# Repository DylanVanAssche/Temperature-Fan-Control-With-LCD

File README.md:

Temperature Fan Control With LCD
================================

A fan controlled by a temperaturesensor and an Arduino. The current temperature (in °C) and fanpower (in %) is shown on a LCD display.

Produced by Dylan Van Assche (2013). I'm not responsible for any damage to your stuff!

Libraries for EAGLE: 
* http://www.faludi.com/2008/10/07/arduino-avr-library-for-eagle-layout-editor/
* https://github.com/zumbik/Eagle-Libraries/blob/master/lm35.lbr

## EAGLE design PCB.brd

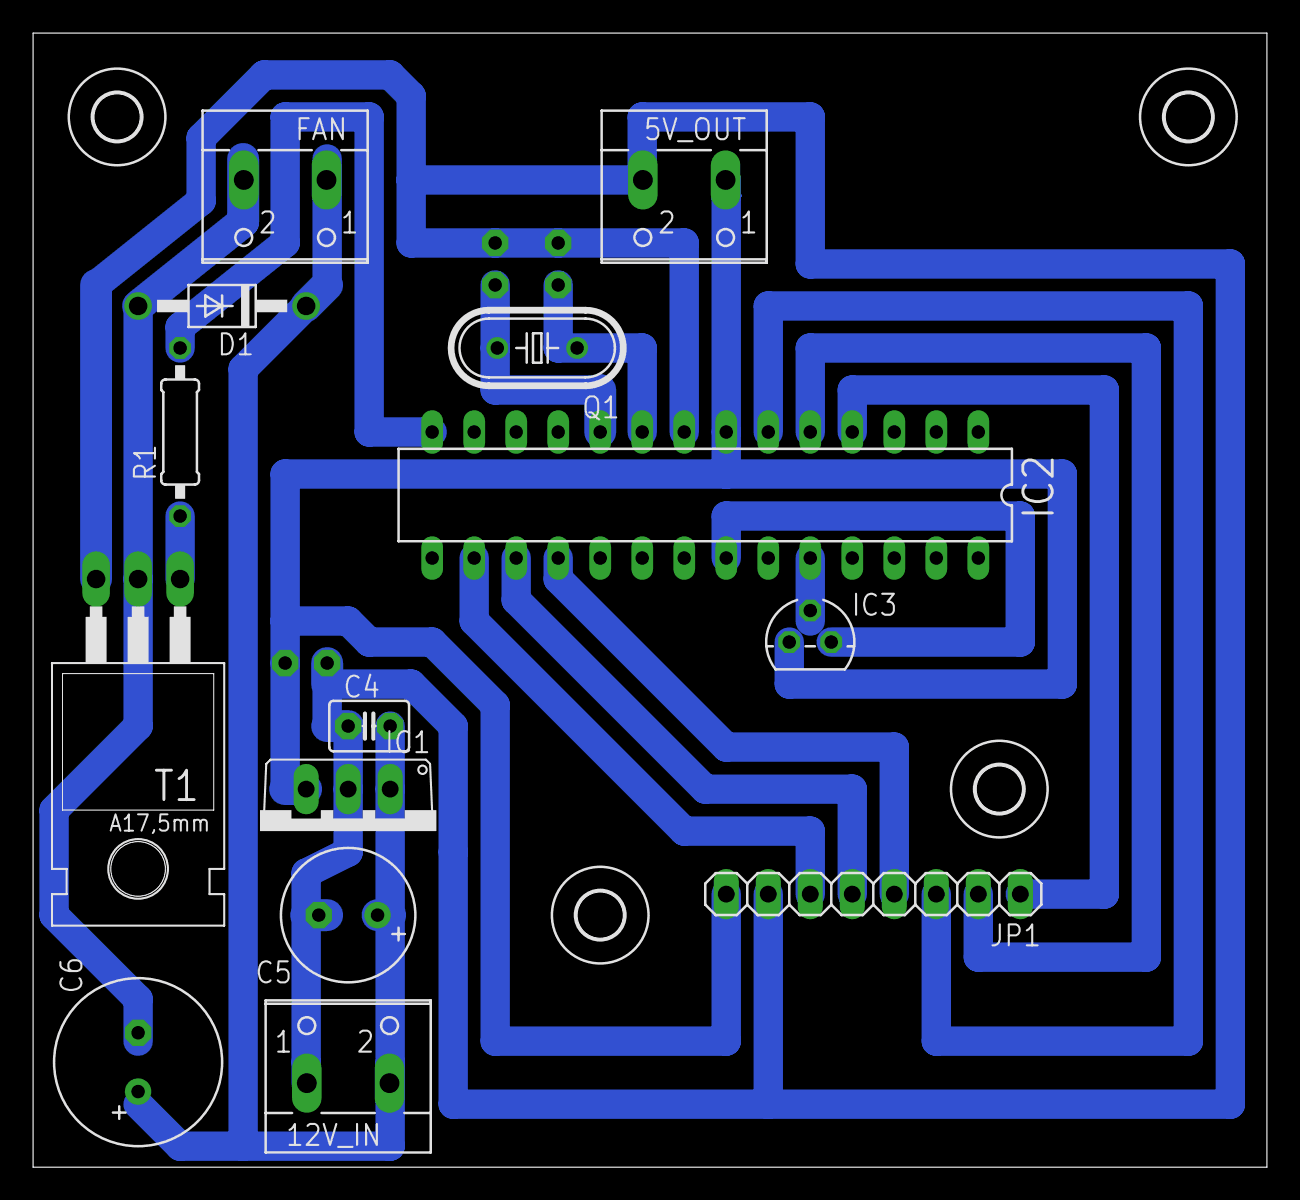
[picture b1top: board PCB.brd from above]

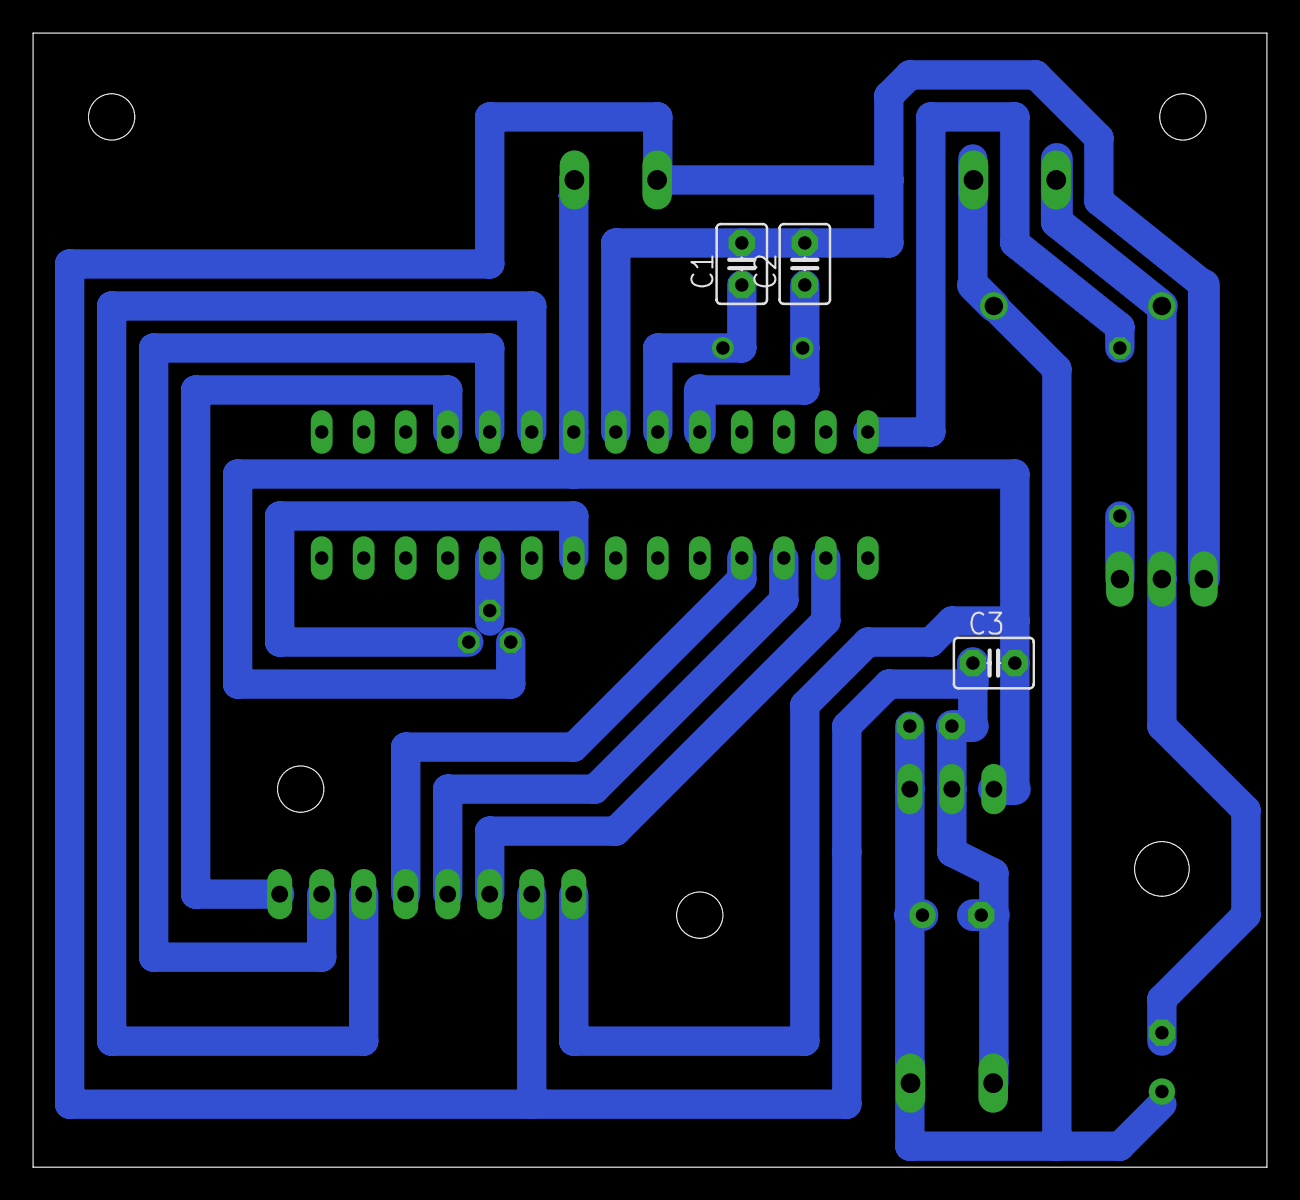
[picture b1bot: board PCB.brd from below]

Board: 2 copper layers, 74.6 x 68.6 mm, 21 parts (3 on the bottom side), 16 nets.

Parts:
5V_OUT, 12V_IN: W237-102
C1, C2: 22 pF; C2.5-3
C3, C4: 100 nF; C2.5-3
C5: 1000 uF; E3,5-8
C6: 2200uF; E3,5-10
D1: 1N4004; DO41-10
FAN: W237-102
H1, H2, H3, H4: MOUNT-HOLE2.8; 2,8
IC1: 7805TV; TO220V
IC2: ATMEGA168-PU; DIL28-3
IC3: LM35CZ; TO92
JP1: LCD; 1X08
Q1: HC49U-V
R1: 0207/10
T1: TIP122; TO220

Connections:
GND: 5V_OUT.2, C1.2, C2.2, IC2.8, IC2.22, IC3.3, JP1.7, T1.3
unnamed: C1.1, IC2.9, Q1.1
unnamed: IC2.16, JP1.6
unnamed: C6.-, D1.A, FAN.2, T1.2
unnamed: C2.1, IC2.10, Q1.2
unnamed: 12V_IN.1, C3.1, C4.1, C5.-, IC1.2
unnamed: IC2.4, JP1.1
unnamed: IC2.5, JP1.2
unnamed: IC2.6, JP1.3
unnamed: R1.1, T1.1
unnamed: IC2.17, JP1.5
unnamed: IC2.18, JP1.4
unnamed: IC2.14, R1.2
unnamed: IC2.24, IC3.2
unnamed: 12V_IN.2, C4.2, C5.+, C6.+, D1.C, FAN.1, IC1.1
VCC: 5V_OUT.1, C3.2, IC1.3, IC2.7, IC3.1, JP1.8

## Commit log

2013-12-13 TemperatureFanControlLCD V1.0.1 RC
    The first stable release. Tested on an Arduino UNO.
2013-12-20 EAGLE file for the PCB of this project
2013-12-20 Extra information!
    For this board I used the Arduino library for EAGLE. You can find it also in this repository.
2013-12-21 Update V1.1
    Bugfix: 7805 voltage regulator wiring.
2014-01-11 Decoupling capacitor added and resistor
    Decoupling capacitor added for driving higher current without noise.
2014-01-11 Update V1.2
    Decoupling capacitor + resistor
